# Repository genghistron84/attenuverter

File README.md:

# attenuverter
Minimal footprint version of Skull &amp; Circuits Attenuverter

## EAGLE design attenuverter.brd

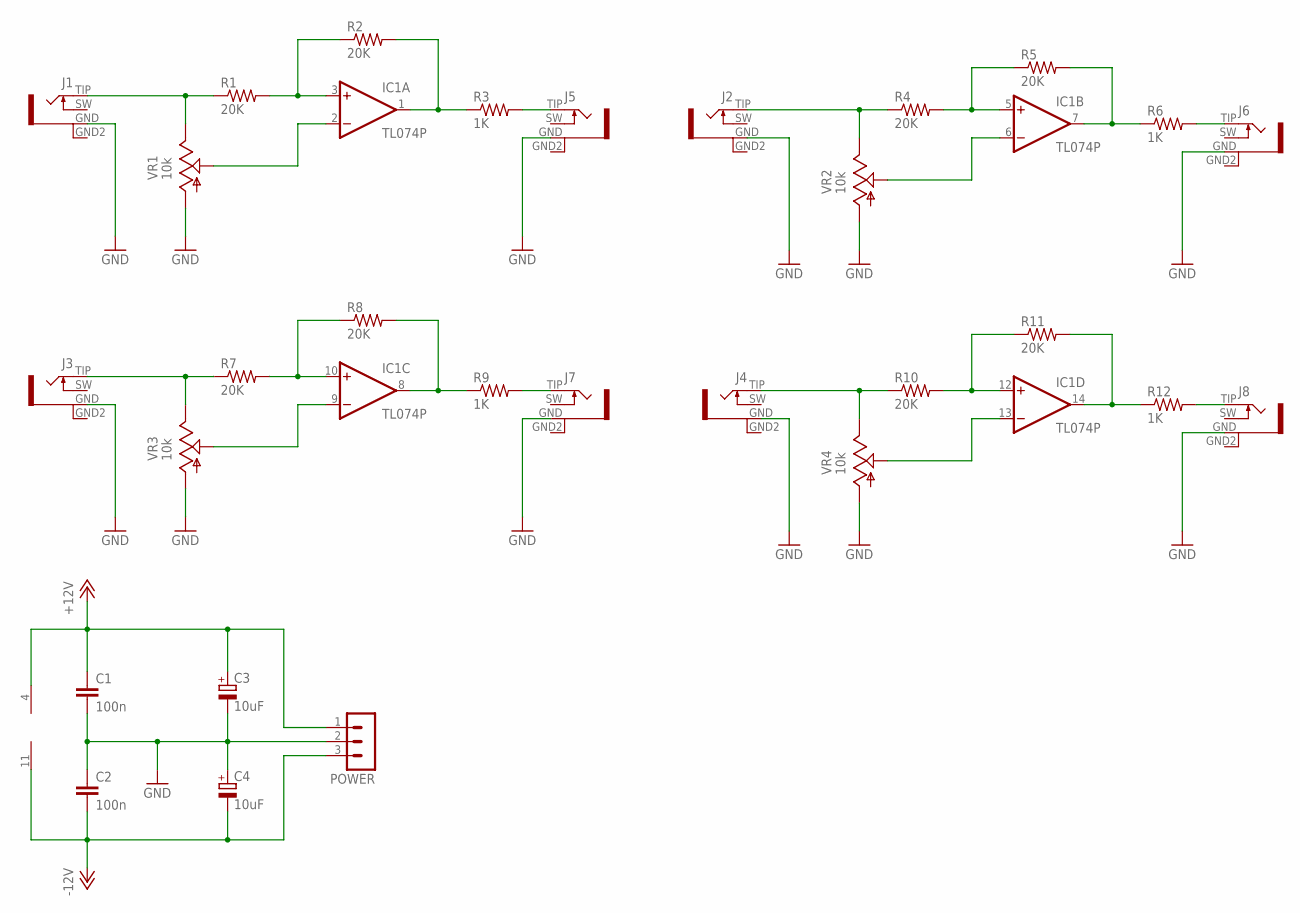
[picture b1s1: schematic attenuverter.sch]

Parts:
C1, C2: 100n; C025-025X050
C3, C4: 10uF; E2,5-6E
IC1: TL074P; DIL14
J1, J2, J3, J4, J5, J6, J7, J8: PJ301WQP; THONK_JACK_P
POWER: MA03-1
R1, R2, R4, R5, R7, R8, R10, R11: 20K; 0207/10
R3, R6, R9, R12: 1K; 0207/10
VR1, VR2, VR3, VR4: 10k; 9MM_SNAP-IN_POT

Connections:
+12V: C1.1, C3.+, IC1.4 (V+), POWER.1
-12V: C2.2, C4.-, IC1.11 (V-), POWER.3
GND: C1.2, C2.1, C3.-, C4.+, J1.GND (1), J2.GND (1), J3.GND (1), J4.GND (1), J5.GND (1), J6.GND (1), J7.GND (1), J8.GND (1), POWER.2, VR1.1 (A), VR2.1 (A), VR3.1 (A), VR4.1 (A)
unnamed: J1.TIP (2), R1.1, VR1.3 (E)
unnamed: J3.TIP (2), R7.1, VR3.3 (E)
unnamed: IC1.10 (+IN), R7.2, R8.1
unnamed: IC1.3 (+IN), R1.2, R2.1
unnamed: IC1.1 (OUT), R2.2, R3.1
unnamed: J5.TIP (2), R3.2
unnamed: IC1.8 (OUT), R8.2, R9.1
unnamed: J7.TIP (2), R9.2
unnamed: IC1.12 (+IN), R10.2, R11.1
unnamed: J4.TIP (2), R10.1, VR4.3 (E)
unnamed: IC1.5 (+IN), R4.2, R5.1
unnamed: J2.TIP (2), R4.1, VR2.3 (E)
unnamed: IC1.7 (OUT), R5.2, R6.1
unnamed: J6.TIP (2), R6.2
unnamed: IC1.14 (OUT), R11.2, R12.1
unnamed: J8.TIP (2), R12.2
unnamed: IC1.2 (-IN), VR1.2 (S)
unnamed: IC1.9 (-IN), VR3.2 (S)
unnamed: IC1.6 (-IN), VR2.2 (S)
unnamed: IC1.13 (-IN), VR4.2 (S)

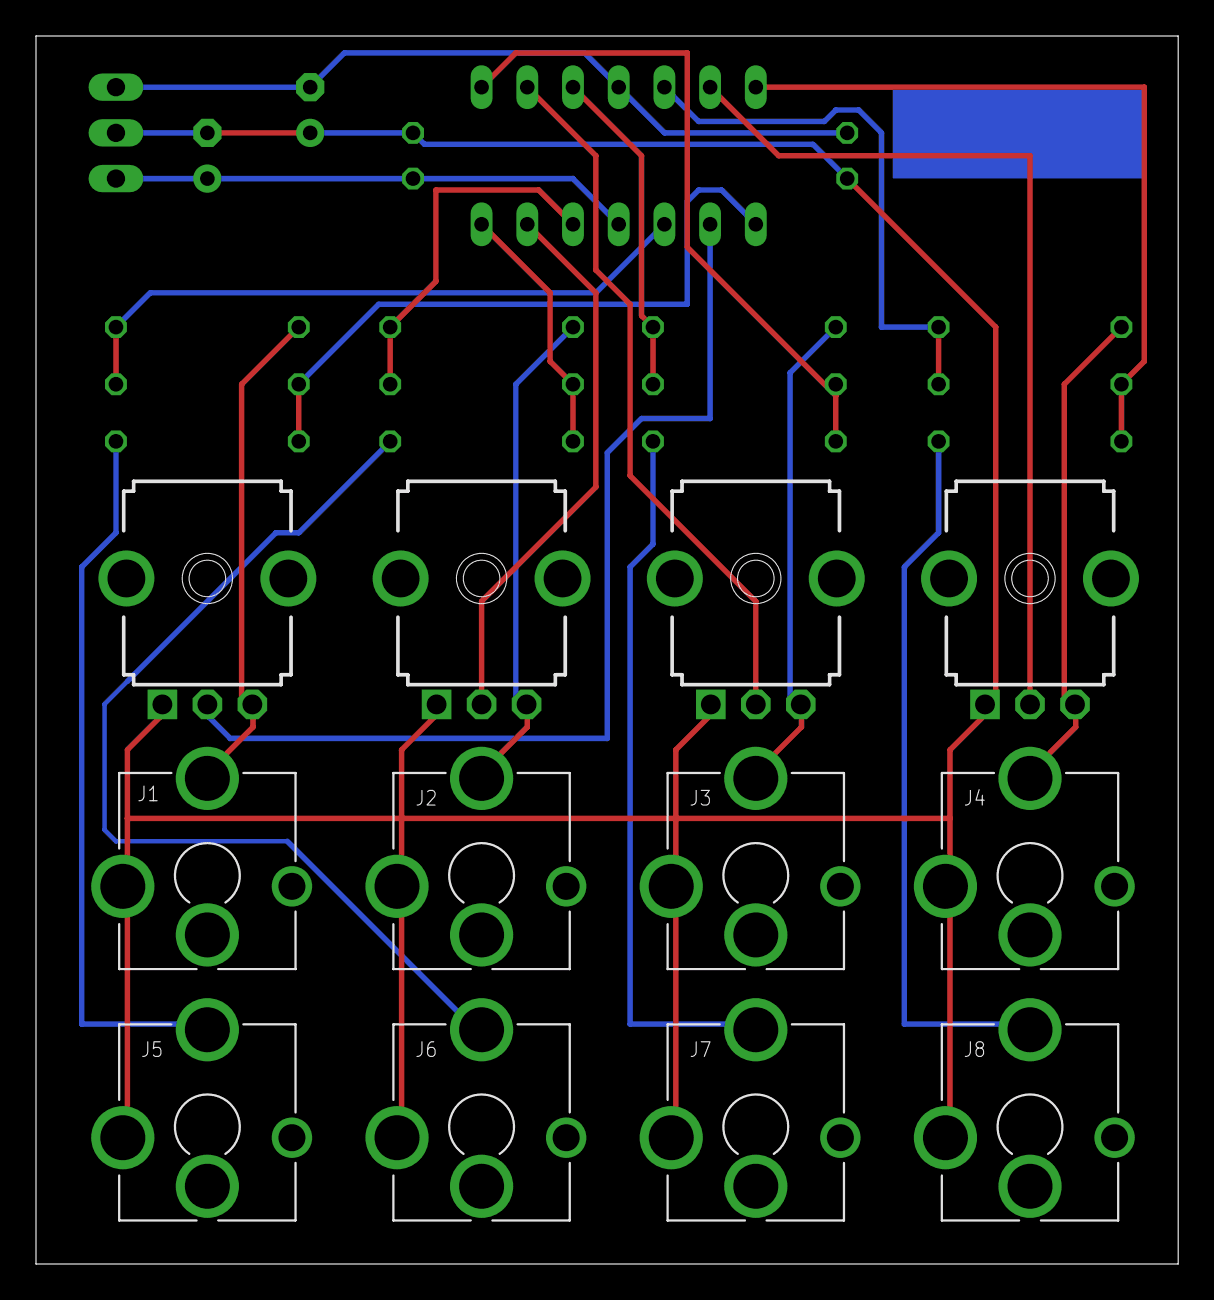
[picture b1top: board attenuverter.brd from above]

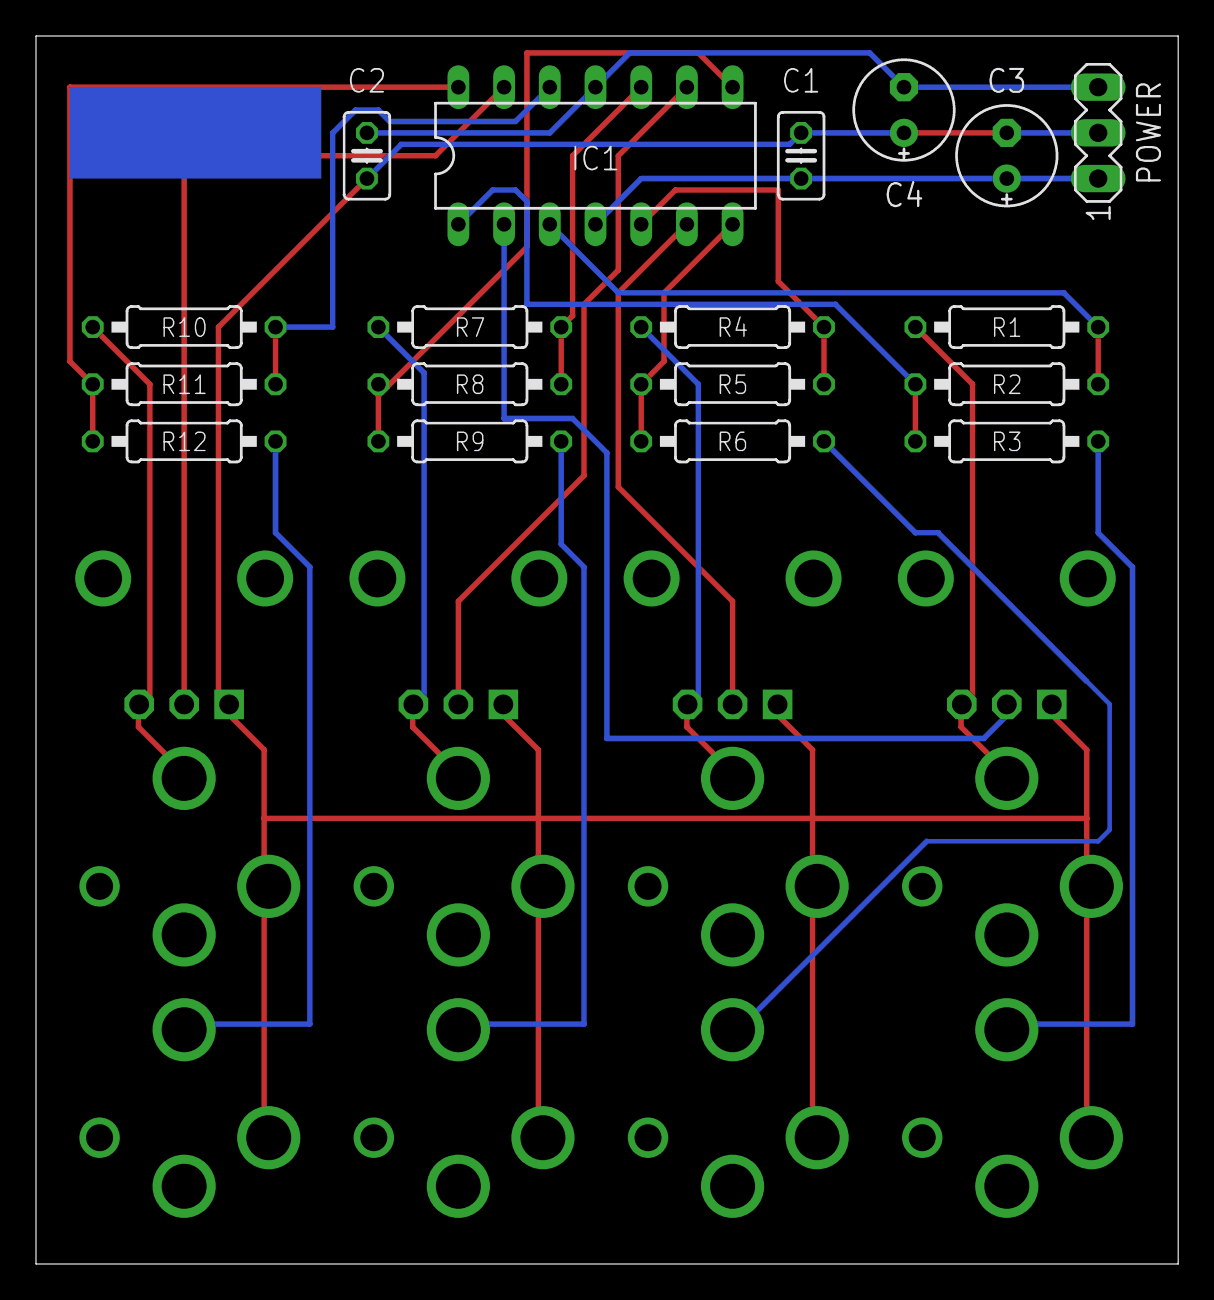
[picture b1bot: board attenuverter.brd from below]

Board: 2 copper layers, 63.5 x 68.2 mm, 30 parts (18 on the bottom side), 23 nets.
